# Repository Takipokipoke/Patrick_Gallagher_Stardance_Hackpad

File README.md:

# Patrick_Gallagher_Stardance_Hackpad
Hackpad/macro keyboard made for the hack club stardance challange

It features a 2x3 'hot programable' keyboard array set up to work with vial.

# Features: 
2x3 ortho layout keyboard
support for 'hot programing' with vial

# CAD model
The case has a stairstep design to hold the pcb and cover at different levels.
It is two seperate pieces.

# PCB:
My PCB was designed in KiCad
The PCB is designed to also have an encoder and screen but I have not worked that in yet.

Schematic:

PCB:

# Firmware:
The firmware I used is QMK
There are 6 keys that are reprogramible with VIAL

# BOM
3d Printed Case (2 Parts)
1 unsoldered Seeed XIAO RP2040
6x MX-Style switches
6x through-hole 1N4148 Diodes
6x white blank DSA keycaps

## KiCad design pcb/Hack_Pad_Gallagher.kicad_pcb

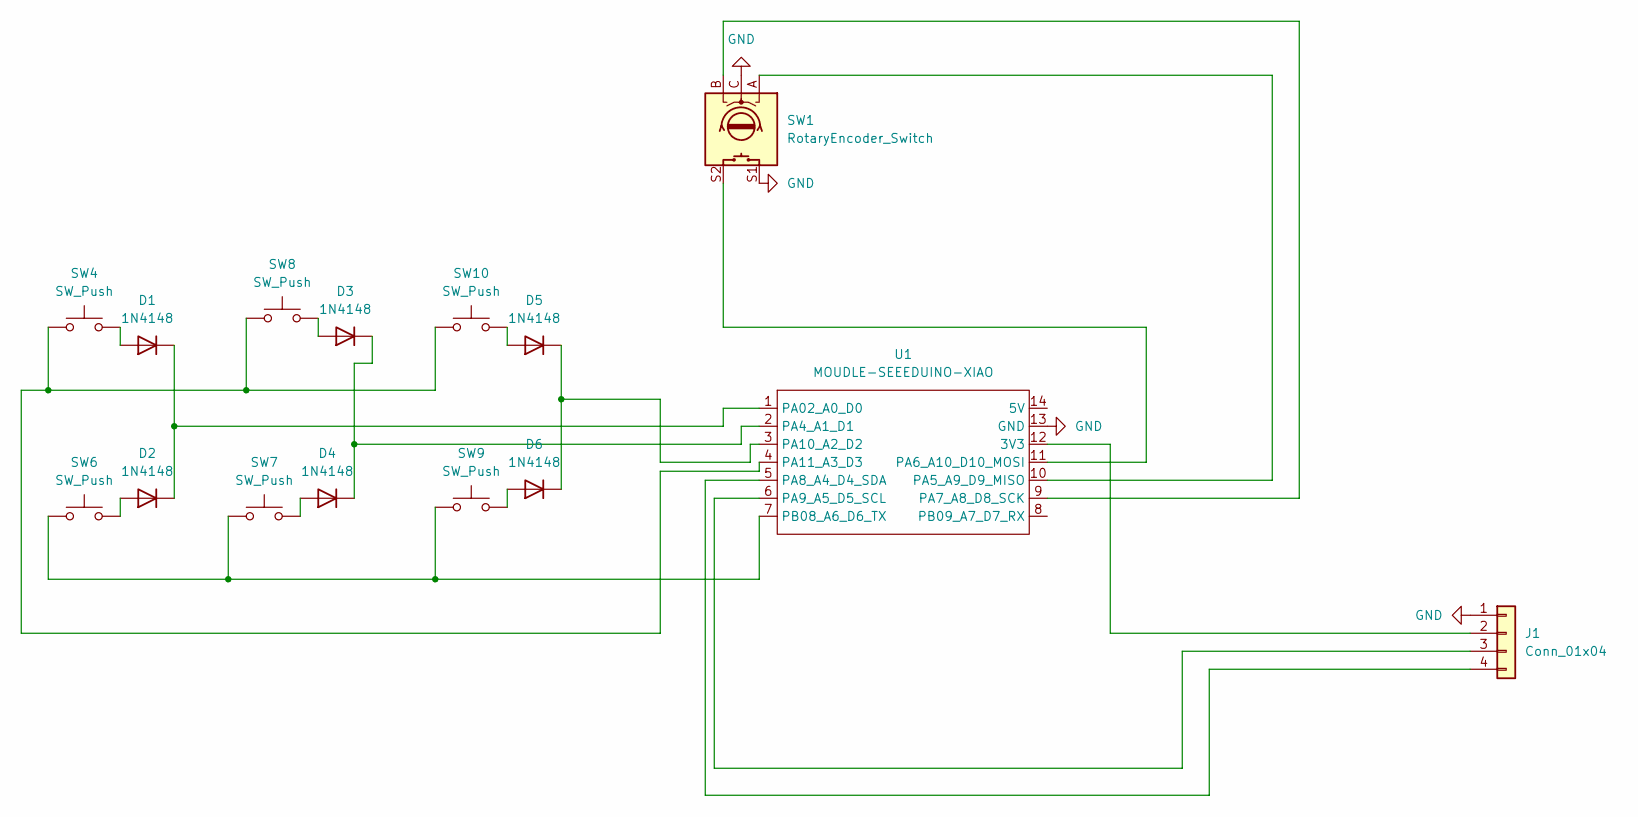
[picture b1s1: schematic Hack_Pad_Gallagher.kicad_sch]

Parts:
D1, D2, D3, D4, D5, D6: 1N4148; D_DO-35_SOD27_P7.62mm_Horizontal
J1: Conn_01x04; FanPinHeader_1x04_P2.54mm_Vertical
SW1: RotaryEncoder_Switch; RotaryEncoder_Alps_EC11E-Switch_Vertical_H20mm
SW4, SW6, SW7, SW8, SW9, SW10: SW_Push; SW_Cherry_MX_1.00u_PCB
U1: MOUDLE-SEEEDUINO-XIAO; XIAO-Generic-Hybrid-14P-2.54-21X17.8MM

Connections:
GND: J1.1, SW1.C, SW1.S1, U1.13 (GND)
unnamed: D1.2 (A), SW4.2
unnamed: D1.1 (K), D2.1 (K), U1.1 (PA02_A0_D0)
unnamed: D2.2 (A), SW6.2
unnamed: D3.2 (A), SW8.2
unnamed: D3.1 (K), D4.1 (K), U1.2 (PA4_A1_D1)
unnamed: D4.2 (A), SW7.2
unnamed: D5.2 (A), SW10.2
unnamed: D5.1 (K), D6.1 (K), U1.3 (PA10_A2_D2)
unnamed: D6.2 (A), SW9.2
unnamed: J1.2, U1.12 (3V3)
unnamed: J1.3, U1.6 (PA9_A5_D5_SCL)
unnamed: J1.4, U1.5 (PA8_A4_D4_SDA)
unnamed: SW1.A, U1.10 (PA5_A9_D9_MISO)
unnamed: SW1.S2, U1.11 (PA6_A10_D10_MOSI)
unnamed: SW1.B, U1.9 (PA7_A8_D8_SCK)
unnamed: SW4.1, SW8.1, SW10.1, U1.4 (PA11_A3_D3)
unnamed: SW6.1, SW7.1, SW9.1, U1.7 (PB08_A6_D6_TX)

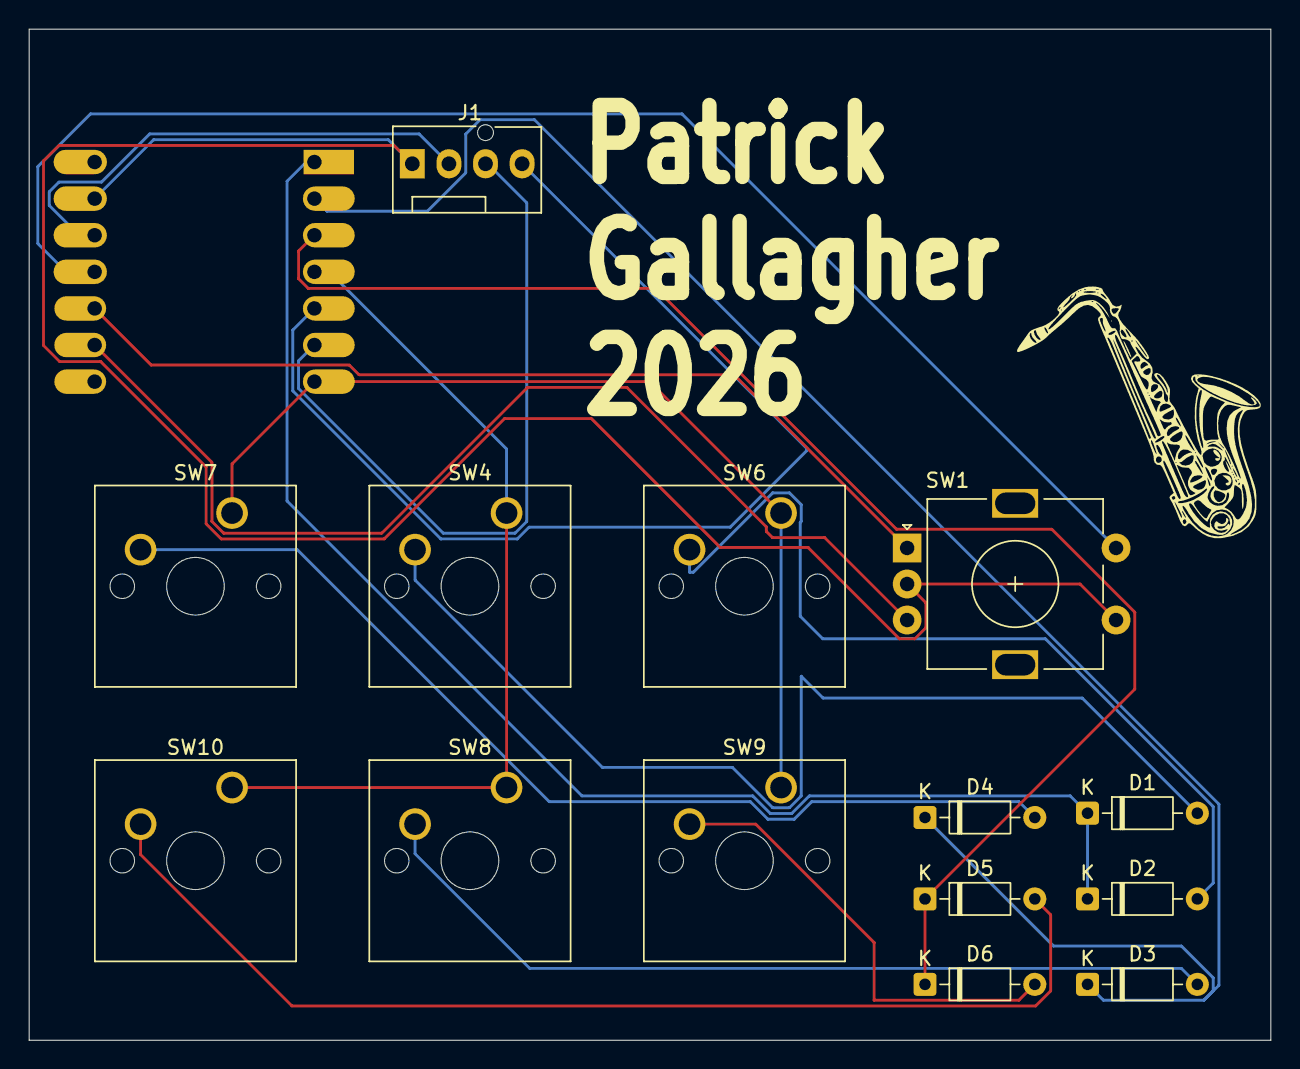
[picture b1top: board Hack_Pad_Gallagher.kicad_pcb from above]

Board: 2 copper layers, 86.2 x 70.2 mm, 15 parts (1 on the bottom side), 18 nets.
